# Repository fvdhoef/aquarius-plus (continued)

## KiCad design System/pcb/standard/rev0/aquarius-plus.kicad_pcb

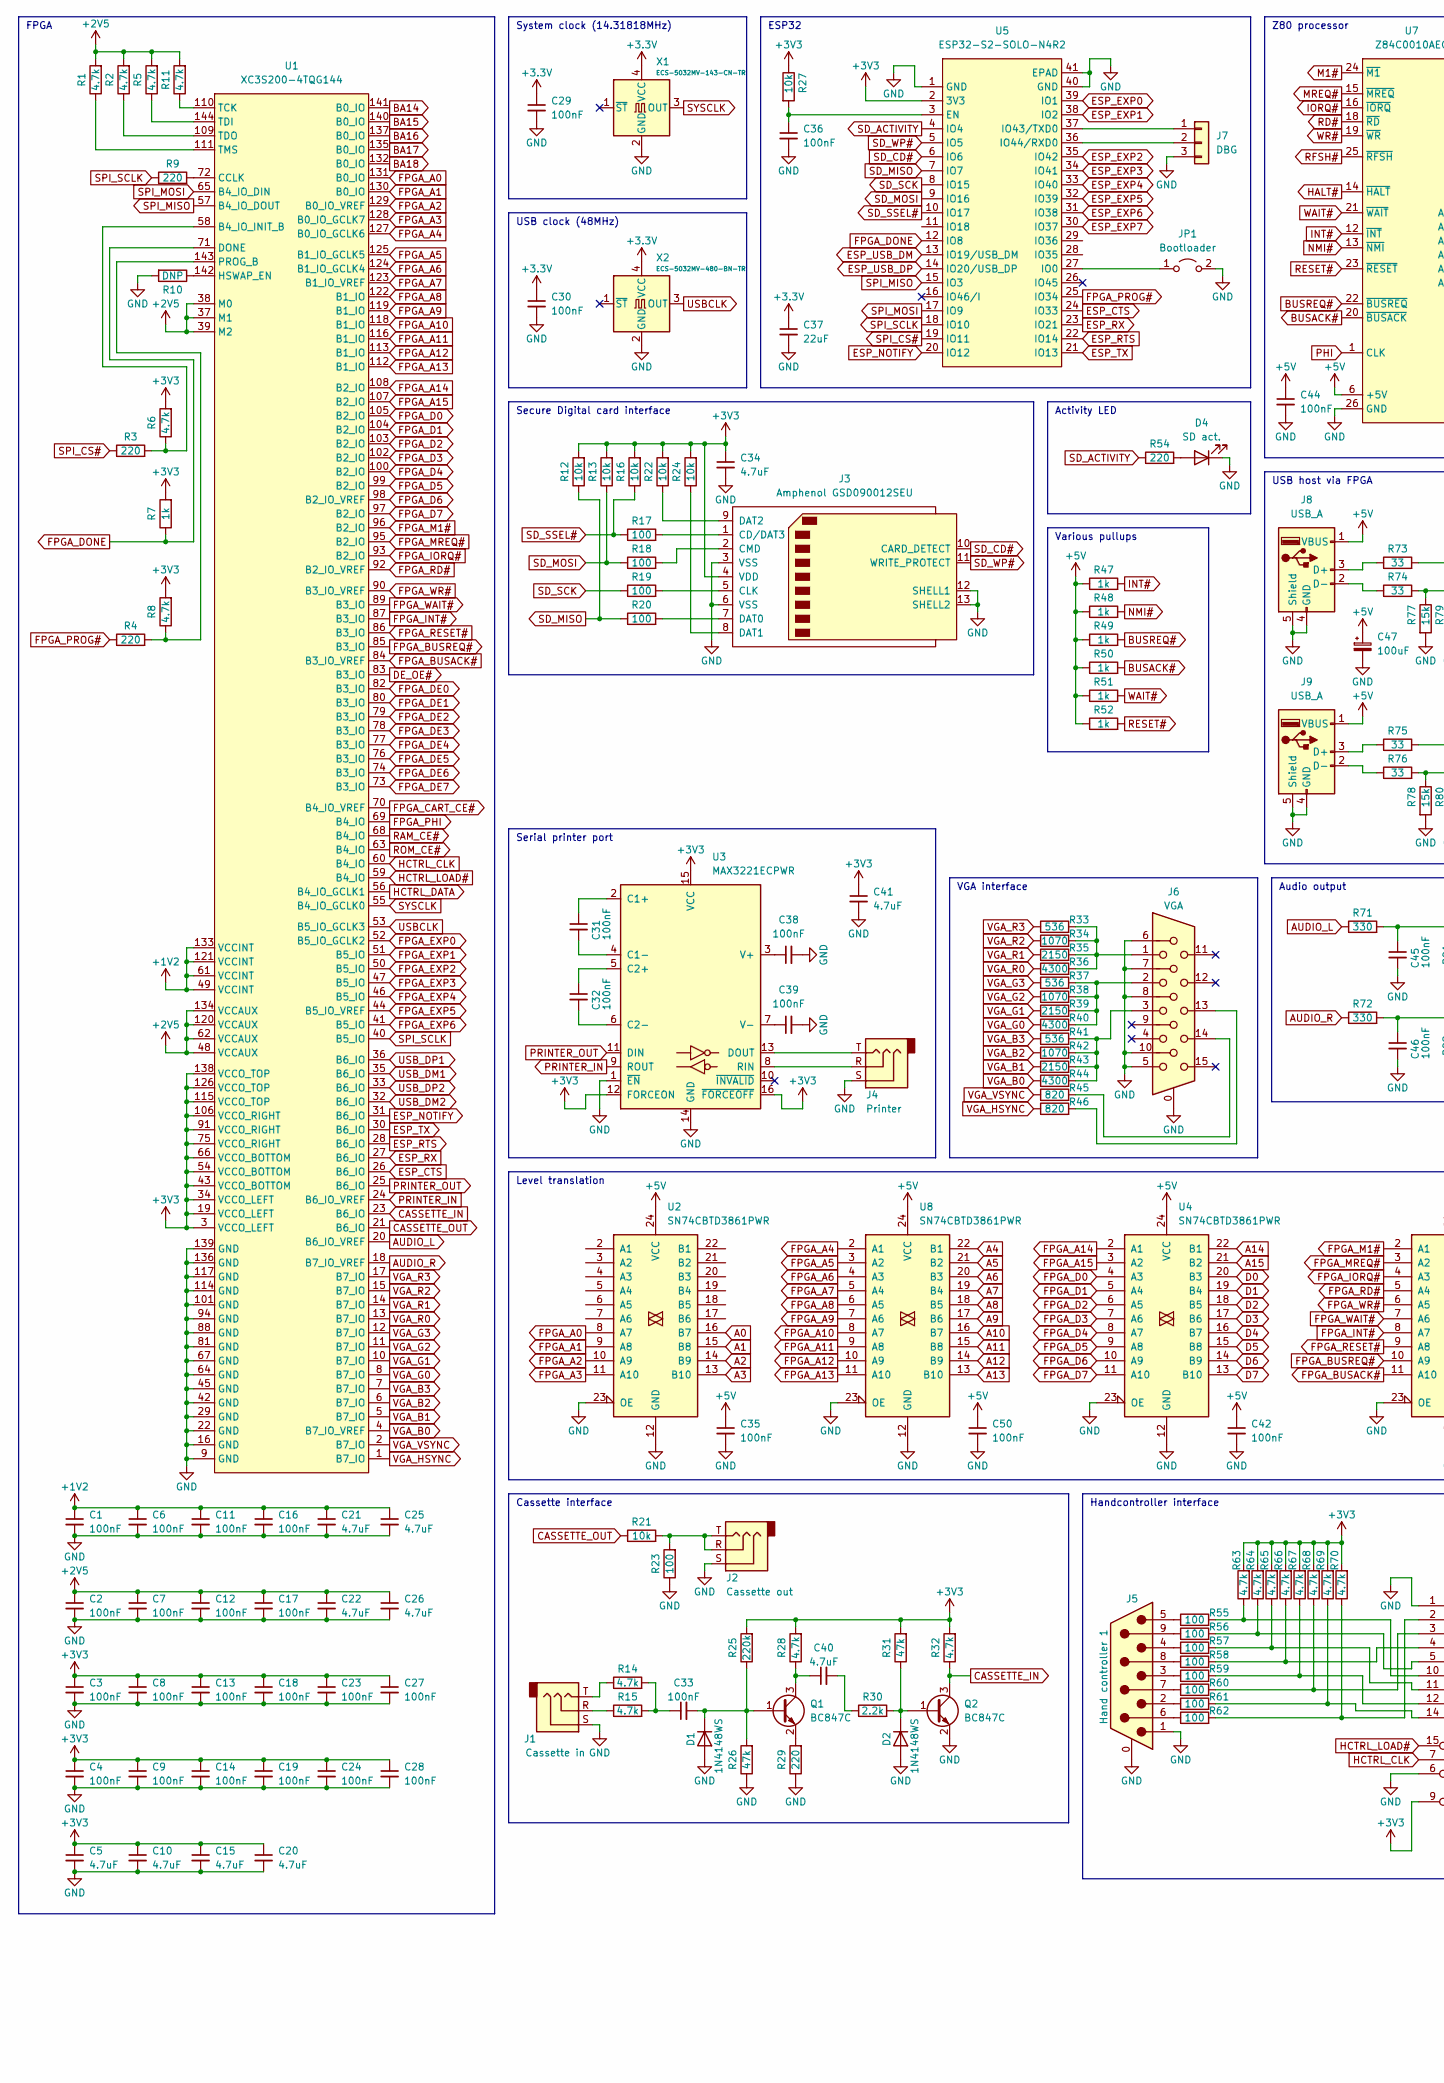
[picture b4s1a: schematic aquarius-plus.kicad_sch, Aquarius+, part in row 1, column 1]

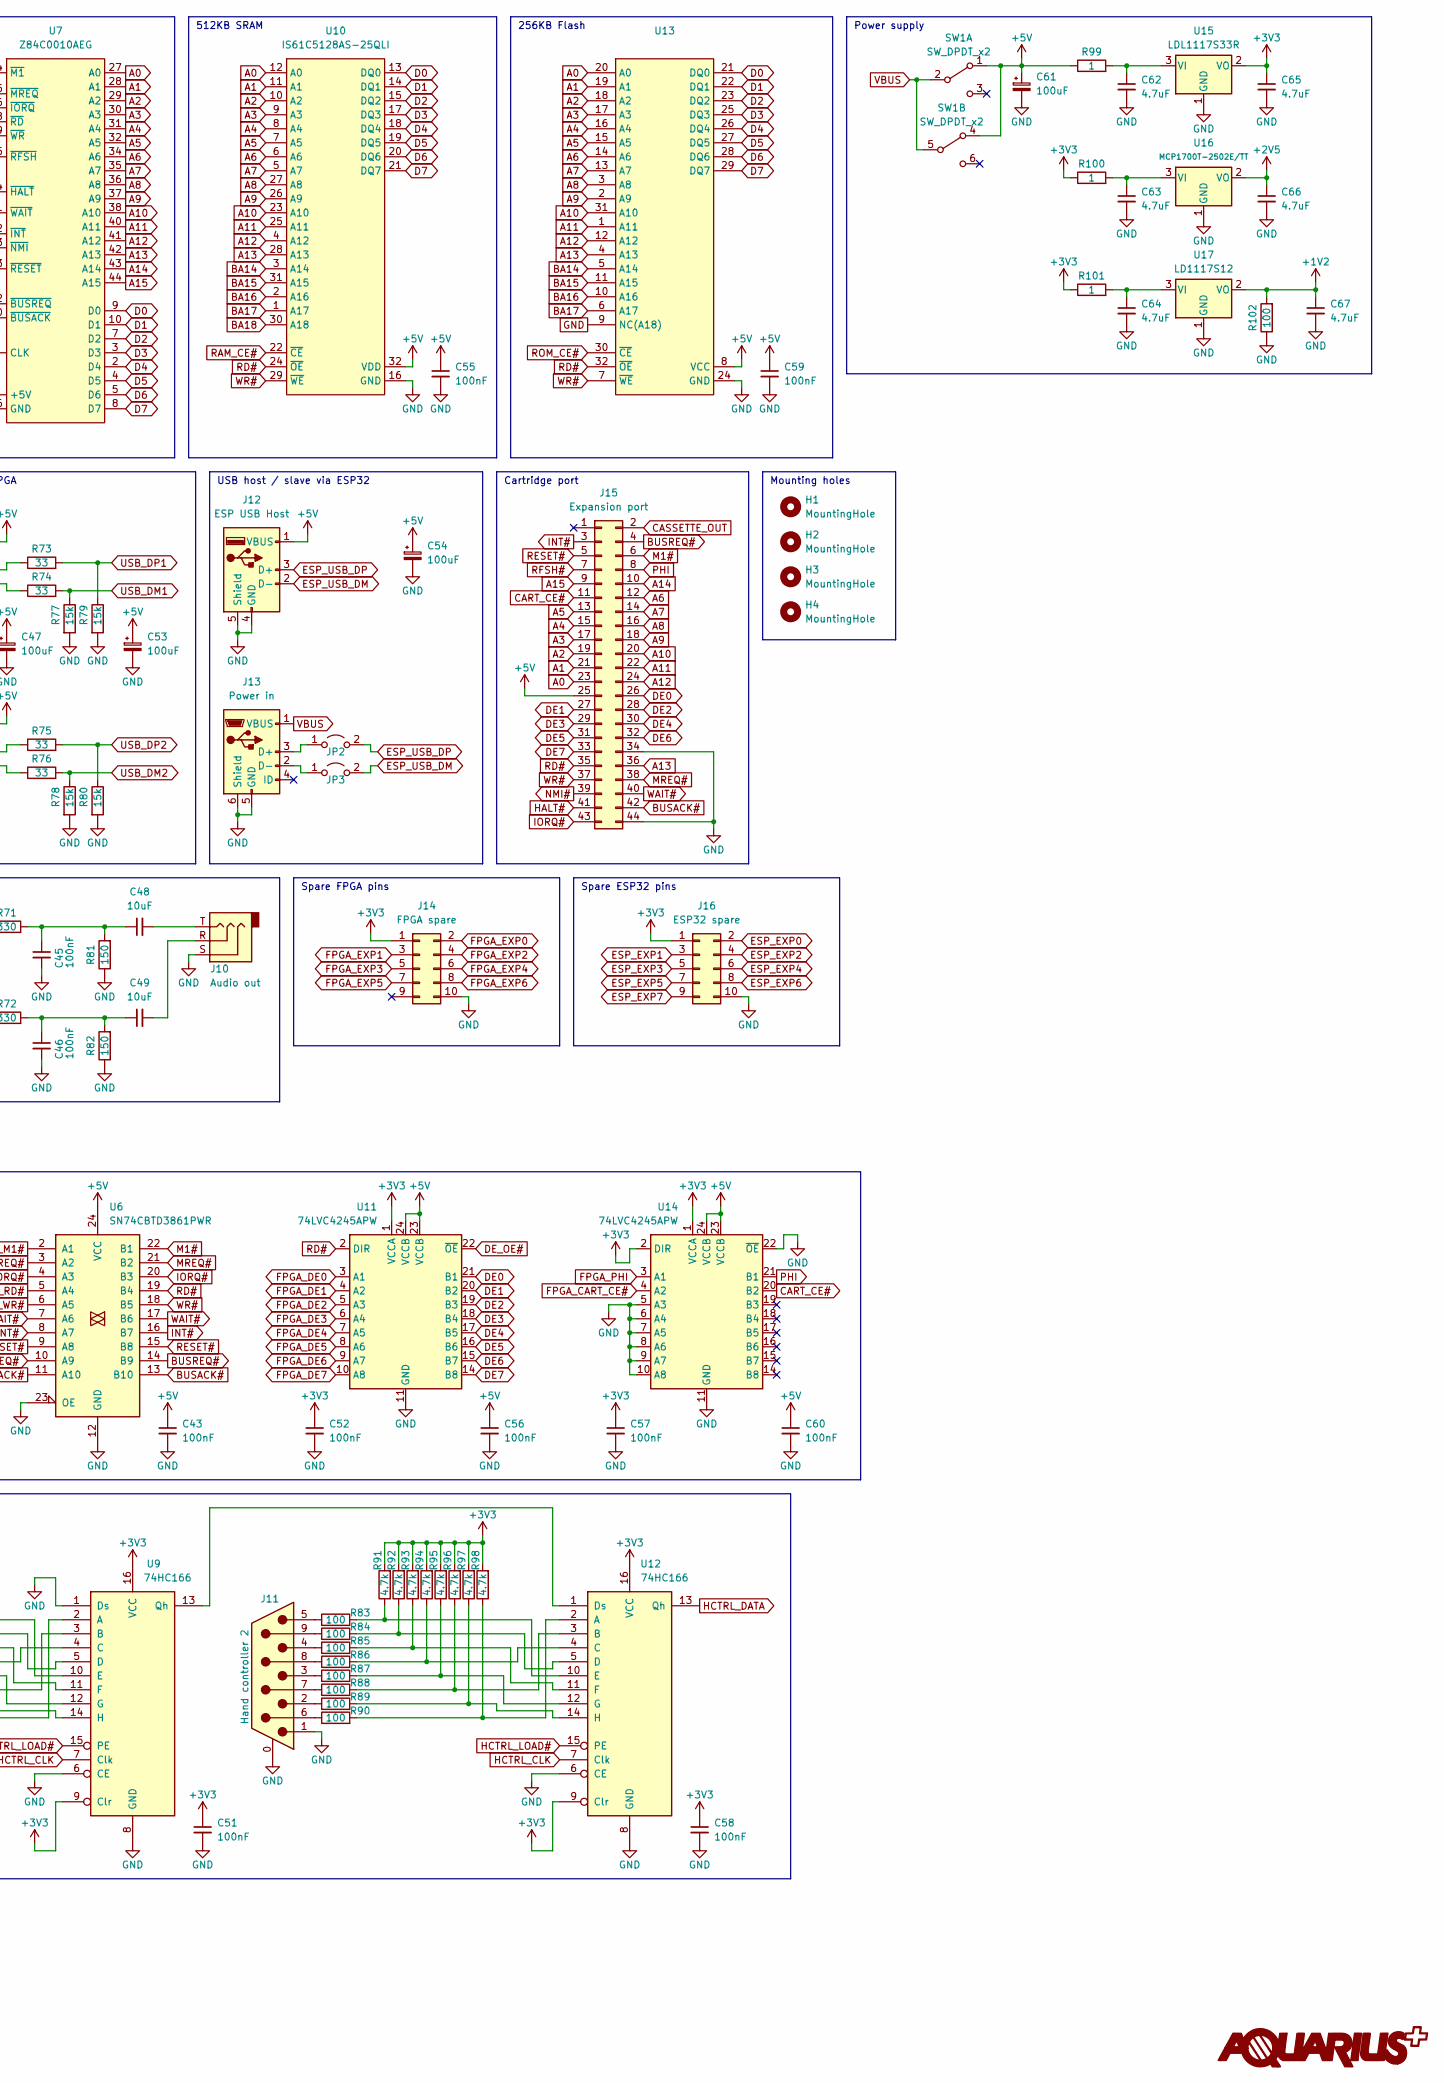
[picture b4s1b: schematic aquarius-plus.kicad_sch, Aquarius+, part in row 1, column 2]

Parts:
C1, C2, C3, C4, C6, C7, C8, C9, C11, C12, C13, C14, C16, C17, C18, C19, C23, C24, C27, C28, C29, C30, C31, C32, C33, C35, C36, C38, C39, C42, C43, C44, C45, C46, C50, C51, C52, C55, C56, C57, C58, C59, C60: 100nF; C_0603_1608Metric
C5, C10, C15, C20, C21, C22, C25, C26, C34, C40, C41, C62, C63, C64, C65, C66, C67: 4.7uF; C_0603_1608Metric
C37: 22uF; C_1206_3216Metric
C47, C53, C54, C61: 100uF; CP_Elec_6.3x7.7
C48, C49: 10uF; C_0805_2012Metric
D1, D2: 1N4148WS; D_SOD-323_HandSoldering
D4: SD act.; LED_D3.0mm_Horizontal_O1.27mm_Z2.0mm
H1, H2, H3, H4: MountingHole; MountingHole_3.2mm_M3
J1: Cassette in; Jack_3.5mm_CUI_SJ-3523-SMT_Horizontal
J2: Cassette out; Jack_3.5mm_CUI_SJ-3523-SMT_Horizontal
J3: Amphenol GSD090012SEU; SD_TE_2041021
J4: Printer; Jack_3.5mm_CUI_SJ-3523-SMT_Horizontal
J5: Hand controller 1; DSUB-9_Male_Horizontal_P2.77x2.84mm_EdgePinOffset9.90mm_Hou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
J6: VGA; ICD15S13E4GV00LF
J7: DBG; PinHeader_1x03_P2.54mm_Vertical
J8, J9: USB_A; USB_A_Molex_67643_Horizontal
J10: Audio out; Jack_3.5mm_CUI_SJ-3523-SMT_Horizontal
J11: Hand controller 2; DSUB-9_Male_Horizontal_P2.77x2.84mm_EdgePinOffset9.90mm_Hou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
J12: ESP USB Host; USB_A_Molex_67643_Horizontal
J13: Power in; 10118193-0001LF
J14: FPGA spare; PinHeader_2x05_P2.54mm_Vertical
J15: Expansion port; CR22A-44D-2.54DSA(70)
J16: ESP32 spare; PinHeader_2x05_P2.54mm_Vertical
JP1: Bootloader; PinHeader_1x02_P2.54mm_Vertical
JP2, JP3: USB; PinHeader_1x02_P2.54mm_Vertical
Q1, Q2: BC847C; SOT-23
R1, R2, R5, R6, R8, R11, R14, R15, R28, R32, R63, R64, R65, R66, R67, R68, R69, R70, R91, R92, R93, R94, R95, R96, R97, R98: 4.7k; R_0603_1608Metric
R3, R4, R9, R29, R54: 220; R_0603_1608Metric
R7, R47, R48, R49, R50, R51, R52: 1k; R_0603_1608Metric
R10: DNP; R_0603_1608Metric
R12, R13, R16, R21, R22, R24, R27: 10k; R_0603_1608Metric
R17, R18, R19, R20, R23, R55, R56, R57, R58, R59, R60, R61, R62, R83, R84, R85, R86, R87, R88, R89, R90, R102: 100; R_0603_1608Metric
R25: 220k; R_0603_1608Metric
R26, R31: 47k; R_0603_1608Metric
R30: 2.2k; R_0603_1608Metric
R33, R37, R41: 536; R_0603_1608Metric
R34, R38, R42: 1070; R_0603_1608Metric
R35, R39, R43: 2150; R_0603_1608Metric
R36, R40, R44: 4300; R_0603_1608Metric
R45, R46: 820; R_0603_1608Metric
R71, R72: 330; R_0603_1608Metric
R73, R74, R75, R76: 33; R_0603_1608Metric
R77, R78, R79, R80: 15k; R_0603_1608Metric
R81, R82: 150; R_0603_1608Metric
R99, R100, R101: 1; R_0603_1608Metric
SW1: SW_DPDT_x2; SW_E-Switch_EG2219_DPDT_Angled
U1: XC3S200-4TQG144; TQFP-144_20x20mm_P0.5mm
U2, U4, U6, U8: SN74CBTD3861PWR; TSSOP-24_4.4x7.8mm_P0.65mm
U3: MAX3221ECPWR; TSSOP-16_4.4x5mm_P0.65mm
U5: ESP32-S2-SOLO-N4R2
U7: Z84C0010AEG; LQFP-44_10x10mm_P0.8mm
U9, U12: 74HC166; SOIC-16_3.9x9.9mm_P1.27mm
U10: IS61C5128AS-25QLI; SSOP-32_11.305x20.495mm_P1.27mm
U11, U14: 74LVC4245APW; TSSOP-24_4.4x7.8mm_P0.65mm
U13: (no value)
U15: LDL1117S33R; SOT-223-3_TabPin2
U16: MCP1700T-2502E/TT; SOT-23
U17: LD1117S12; SOT-223-3_TabPin2
X1: ECS-5032MV-143-CN-TR; Oscillator_SMD_SeikoEpson_SG8002LB-4Pin_5.0x3.2mm
X2: ECS-5032MV-480-BN-TR; Oscillator_SMD_SeikoEpson_SG8002LB-4Pin_5.0x3.2mm

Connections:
+1V2: C1.1, C6.1, C11.1, C16.1, C21.1, C25.1, C67.1, R102.2, U1.49 (VCCINT), U1.61 (VCCINT), U1.121 (VCCINT), U1.133 (VCCINT), U17.2 (VO)
+2V5: C2.1, C7.1, C12.1, C17.1, C22.1, C26.1, C66.1, R1.2, R2.2, R5.2, R11.2, U1.37 (M1), U1.38 (M0), U1.39 (M2), U1.48 (VCCAUX), U1.62 (VCCAUX), U1.120 (VCCAUX), U1.134 (VCCAUX), U16.2 (VO)
+5V: C35.1, C42.1, C43.1, C44.1, C47.1, C50.1, C53.1, C54.1, C55.1, C56.1, C59.1, C60.1, C61.1, J8.1 (VBUS), J9.1 (VBUS), J12.1 (VBUS), J15.25, R47.1, R48.1, R49.1, R50.1, R51.1, R52.1, R99.1, SW1.1 (A), SW1.4 (A), U2.24 (VCC), U4.24 (VCC), U6.24 (VCC), U7.6 (+5V), U8.24 (VCC), U10.32 (VDD), U11.23 (VCCB), U11.24 (VCCB), U13.8 (VCC), U14.23 (VCCB), U14.24 (VCCB)
A0: J15.23, U2.16 (B7), U7.27 (A0), U10.12 (A0), U13.20 (A0)
A1: J15.21, U2.15 (B8), U7.28 (A1), U10.11 (A1), U13.19 (A1)
A2: J15.19, U2.14 (B9), U7.29 (A2), U10.10 (A2), U13.18 (A2)
A3: J15.17, U2.13 (B10), U7.30 (A3), U10.9 (A3), U13.17 (A3)
A4: J15.15, U7.31 (A4), U8.22 (B1), U10.8 (A4), U13.16 (A4)
A5: J15.13, U7.32 (A5), U8.21 (B2), U10.7 (A5), U13.15 (A5)
A6: J15.12, U7.34 (A6), U8.20 (B3), U10.6 (A6), U13.14 (A6)
A7: J15.14, U7.35 (A7), U8.19 (B4), U10.5 (A7), U13.13 (A7)
A8: J15.16, U7.36 (A8), U8.18 (B5), U10.27 (A8), U13.3 (A8)
A9: J15.18, U7.37 (A9), U8.17 (B6), U10.26 (A9), U13.2 (A9)
A10: J15.20, U7.38 (A10), U8.16 (B7), U10.23 (A10), U13.31 (A10)
A11: J15.22, U7.40 (A11), U8.15 (B8), U10.25 (A11), U13.1 (A11)
A12: J15.24, U7.41 (A12), U8.14 (B9), U10.4 (A12), U13.12 (A12)
A13: J15.36, U7.42 (A13), U8.13 (B10), U10.28 (A13), U13.4 (A13)
A14: J15.10, U4.22 (B1), U7.43 (A14)
A15: J15.9, U4.21 (B2), U7.44 (A15)
AUDIO_L: R71.1, U1.20 (B6_IO_VREF)
AUDIO_R: R72.1, U1.18 (B7_IO_VREF)
BA14: U1.141 (B0_IO), U10.3 (A14), U13.5 (A14)
BA15: U1.140 (B0_IO), U10.31 (A15), U13.11 (A15)
BA16: U1.137 (B0_IO), U10.2 (A16), U13.10 (A16)
BA17: U1.135 (B0_IO), U10.1 (A17), U13.6 (A17)
BA18: U1.132 (B0_IO), U10.30 (A18)
BUSACK#: J15.42, R50.2, U6.13 (B10), U7.20 (~BUSACK)
BUSREQ#: J15.4, R49.2, U6.14 (B9), U7.22 (~BUSREQ)
CART_CE#: J15.11, U14.20 (B2)
CASSETTE_IN: Q2.3 (C), R32.1, U1.23 (B6_IO)
CASSETTE_OUT: J15.2, R21.1, U1.21 (B6_IO)
D0: U4.20 (B3), U7.9 (D0), U10.13 (DQ0), U13.21 (DQ0)
D1: U4.19 (B4), U7.10 (D1), U10.14 (DQ1), U13.22 (DQ1)
D2: U4.18 (B5), U7.7 (D2), U10.15 (DQ2), U13.23 (DQ2)
D3: U4.17 (B6), U7.3 (D3), U10.17 (DQ3), U13.25 (DQ3)
D4: U4.16 (B7), U7.2 (D4), U10.18 (DQ4), U13.26 (DQ4)
D5: U4.15 (B8), U7.4 (D5), U10.19 (DQ5), U13.27 (DQ5)
D6: U4.14 (B9), U7.5 (D6), U10.20 (DQ6), U13.28 (DQ6)
D7: U4.13 (B10), U7.8 (D7), U10.21 (DQ7), U13.29 (DQ7)
DE0: J15.26, U11.21 (B1)
DE1: J15.27, U11.20 (B2)
DE2: J15.28, U11.19 (B3)
DE3: J15.29, U11.18 (B4)
DE4: J15.30, U11.17 (B5)
DE5: J15.31, U11.16 (B6)
DE6: J15.32, U11.15 (B7)
DE7: J15.33, U11.14 (B8)
DE_OE#: U1.83 (B3_IO), U11.22 (~OE)
ESP_CTS: U1.26 (B6_IO), U5.24 (IO33)
ESP_EXP0: J16.2, U5.39 (IO1)
ESP_EXP1: J16.3, U5.38 (IO2)
ESP_EXP2: J16.4, U5.35 (IO42)
ESP_EXP3: J16.5, U5.34 (IO41)
ESP_EXP4: J16.6, U5.33 (IO40)
ESP_EXP5: J16.7, U5.32 (IO39)
ESP_EXP6: J16.8, U5.31 (IO38)
ESP_EXP7: J16.9, U5.30 (IO37)
ESP_NOTIFY: U1.31 (B6_IO), U5.20 (IO12)
ESP_RTS: U1.28 (B6_IO), U5.22 (IO14)
ESP_RX: U1.27 (B6_IO), U5.23 (IO21)
ESP_TX: U1.30 (B6_IO), U5.21 (IO13)
ESP_USB_DM: J12.2 (D-), JP3.2 (B), U5.13 (IO19/USB_DM)
ESP_USB_DP: J12.3 (D+), JP2.2 (B), U5.14 (IO20/USB_DP)
FPGA_A0: U1.131 (B0_IO), U2.8 (A7)
FPGA_A1: U1.130 (B0_IO), U2.9 (A8)
FPGA_A2: U1.129 (B0_IO_VREF), U2.10 (A9)
FPGA_A3: U1.128 (B0_IO_GCLK7), U2.11 (A10)
FPGA_A4: U1.127 (B0_IO_GCLK6), U8.2 (A1)
FPGA_A5: U1.125 (B1_IO_GCLK5), U8.3 (A2)
FPGA_A6: U1.124 (B1_IO_GCLK4), U8.4 (A3)
FPGA_A7: U1.123 (B1_IO_VREF), U8.5 (A4)
FPGA_A8: U1.122 (B1_IO), U8.6 (A5)
FPGA_A9: U1.119 (B1_IO), U8.7 (A6)
FPGA_A10: U1.118 (B1_IO), U8.8 (A7)
FPGA_A11: U1.116 (B1_IO), U8.9 (A8)
FPGA_A12: U1.113 (B1_IO), U8.10 (A9)
FPGA_A13: U1.112 (B1_IO), U8.11 (A10)
FPGA_A14: U1.108 (B2_IO), U4.2 (A1)
FPGA_A15: U1.107 (B2_IO), U4.3 (A2)
FPGA_BUSACK#: U1.84 (B3_IO_VREF), U6.11 (A10)
FPGA_BUSREQ#: U1.85 (B3_IO), U6.10 (A9)
FPGA_CART_CE#: U1.70 (B4_IO_VREF), U14.4 (A2)
FPGA_D0: U1.105 (B2_IO), U4.4 (A3)
FPGA_D1: U1.104 (B2_IO), U4.5 (A4)
FPGA_D2: U1.103 (B2_IO), U4.6 (A5)
FPGA_D3: U1.102 (B2_IO), U4.7 (A6)
FPGA_D4: U1.100 (B2_IO), U4.8 (A7)
FPGA_D5: U1.99 (B2_IO), U4.9 (A8)
FPGA_D6: U1.98 (B2_IO_VREF), U4.10 (A9)
FPGA_D7: U1.97 (B2_IO), U4.11 (A10)
FPGA_DE0: U1.82 (B3_IO), U11.3 (A1)
FPGA_DE1: U1.80 (B3_IO), U11.4 (A2)
FPGA_DE2: U1.79 (B3_IO), U11.5 (A3)
FPGA_DE3: U1.78 (B3_IO), U11.6 (A4)
FPGA_DE4: U1.77 (B3_IO), U11.7 (A5)
FPGA_DE5: U1.76 (B3_IO), U11.8 (A6)
FPGA_DE6: U1.74 (B3_IO), U11.9 (A7)
FPGA_DE7: U1.73 (B3_IO), U11.10 (A8)
FPGA_DONE: R7.1, U1.71 (DONE), U5.12 (IO8)
FPGA_EXP0: J14.2, U1.52 (B5_IO_GCLK2)
FPGA_EXP1: J14.3, U1.51 (B5_IO)
FPGA_EXP2: J14.4, U1.50 (B5_IO)
FPGA_EXP3: J14.5, U1.47 (B5_IO)
FPGA_EXP4: J14.6, U1.46 (B5_IO)
FPGA_EXP5: J14.7, U1.44 (B5_IO_VREF)
FPGA_EXP6: J14.8, U1.41 (B5_IO)
FPGA_INT#: U1.87 (B3_IO), U6.8 (A7)
FPGA_IORQ#: U1.93 (B2_IO), U6.4 (A3)
FPGA_M1#: U1.96 (B2_IO), U6.2 (A1)
FPGA_MREQ#: U1.95 (B2_IO), U6.3 (A2)
FPGA_PHI: U1.69 (B4_IO), U14.3 (A1)
FPGA_PROG#: R4.1, U5.25 (IO34)
FPGA_RD#: U1.92 (B2_IO_VREF), U6.5 (A4)
FPGA_RESET#: U1.86 (B3_IO), U6.9 (A8)
FPGA_WAIT#: U1.89 (B3_IO), U6.7 (A6)
FPGA_WR#: U1.90 (B3_IO_VREF), U6.6 (A5)
GND: C1.2, C2.2, C3.2, C4.2, C5.2, C6.2, C7.2, C8.2, C9.2, C10.2, C11.2, C12.2, C13.2, C14.2, C15.2, C16.2, C17.2, C18.2, C19.2, C20.2, C21.2, C22.2, C23.2, C24.2, C25.2, C26.2, C27.2, C28.2, C29.2, C30.2, C34.2, C35.2, C36.2, C37.2, C38.2, C39.2, C41.2, C42.2, C43.2, C44.2, C45.2, C46.2, C47.2, C50.2, C51.2, C52.2, C53.2, C54.2, C55.2, C56.2, C57.2, C58.2, C59.2, C60.2, C61.2, C62.2, C63.2, C64.2, C65.2, C66.2, C67.2, D1.2 (A), D2.2 (A), D4.1 (K), J1.S, J2.S, J3.3 (VSS), J3.6 (VSS), J3.12 (SHELL1), J3.13 (SHELL2), J4.S, J5.0 (PAD), J5.1, J6.0, J6.5, J6.6, J6.7, J6.8, J6.10, J7.3, J8.4 (GND), J8.5 (Shield), J9.4 (GND), J9.5 (Shield), J10.S, J11.0 (PAD), J11.1, J12.4 (GND), J12.5 (Shield), J13.5 (GND), J13.6 (Shield), J14.10, J15.34, J15.44, J16.10, JP1.2 (B), Q2.2 (E), R10.2, R23.1, R26.1, R29.1, R77.2, R78.2, R79.2, R80.2, R81.1, R82.1, R102.1, U1.9 (GND), U1.16 (GND), U1.22 (GND), U1.29 (GND), U1.42 (GND), U1.45 (GND), U1.64 (GND), U1.67 (GND), U1.81 (GND), U1.88 (GND), U1.94 (GND), U1.101 (GND), U1.114 (GND), U1.117 (GND), U1.136 (GND), U1.139 (GND), U2.12 (GND), U2.23 (OE), U3.1 (~EN), U3.14 (GND), U4.12 (GND), U4.23 (OE), U5.1 (GND), U5.40 (GND), U5.41 (EPAD), U6.12 (GND), U6.23 (OE), U7.26 (GND), U8.12 (GND), U8.23 (OE), U9.1 (Ds), U9.6 (CE), U9.8 (GND), U10.16 (GND), U11.11 (GND), U11.12 (GND), U11.13 (GND), U12.6 (CE), U12.8 (GND), U13.9 (NC(A18)), U13.24 (GND), U14.5 (A3), U14.6 (A4), U14.7 (A5), U14.8 (A6), U14.9 (A7), U14.10 (A8), U14.11 (GND), U14.12 (GND), U14.13 (GND), U14.22 (~OE), U15.1 (GND), U16.1 (GND), U17.1 (GND), X1.2 (GND), X2.2 (GND)
HALT#: J15.41, U7.14 (~HALT)
HCTRL_CLK: U1.60 (B4_IO), U9.7 (Clk), U12.7 (Clk)
HCTRL_DATA: U1.56 (B4_IO_GCLK1), U12.13 (Qh)
HCTRL_LOAD#: U1.59 (B4_IO), U9.15 (PE), U12.15 (PE)
INT#: J15.3, R47.2, U6.16 (B7), U7.12 (~INT)
IORQ#: J15.43, U6.20 (B3), U7.16 (~IORQ)
M1#: J15.6, U6.22 (B1), U7.24 (~M1)
MREQ#: J15.38, U6.21 (B2), U7.15 (~MREQ)
NMI#: J15.39, R48.2, U7.13 (~NMI)
unnamed: C31.1, U3.2 (C1+)
unnamed: C31.2, U3.4 (C1-)
unnamed: C32.1, U3.5 (C2+)
unnamed: C32.2, U3.6 (C2-)
unnamed: C33.1, R14.2, R15.2
unnamed: C33.2, D1.1 (K), Q1.1 (B), R25.1, R26.2
unnamed: C36.1, R27.2, U5.3 (EN)
unnamed: C38.1, U3.3 (V+)
unnamed: C39.1, U3.7 (V-)
unnamed: C40.1, Q1.3 (C), R28.1
unnamed: C40.2, R30.1
unnamed: C45.1, C48.1, R71.2, R81.2
unnamed: C46.1, C49.1, R72.2, R82.2
unnamed: C48.2, J10.T
unnamed: C49.2, J10.R
unnamed: C62.1, R99.2, U15.3 (VI)
unnamed: C63.1, R100.2, U16.3 (VI)
unnamed: C64.1, R101.2, U17.3 (VI)
unnamed: D2.1 (K), Q2.1 (B), R30.2, R31.1
unnamed: D4.2 (A), R54.2
unnamed: J1.R, R15.1
unnamed: J1.T, R14.1
unnamed: J2.R, J2.T, R21.2, R23.2
unnamed: J3.1 (CD/DAT3), R17.2
unnamed: J3.2 (CMD), R18.2
unnamed: J3.5 (CLK), R19.2
unnamed: J3.7 (DAT0), R20.2
unnamed: J3.8 (DAT1), R24.1
unnamed: J3.9 (DAT2), R22.1
unnamed: J4.R, U3.8 (RIN)
unnamed: J4.T, U3.13 (DOUT)
unnamed: J5.2, R61.1
unnamed: J5.3, R59.1
unnamed: J5.4, R57.1
unnamed: J5.5, R55.1
unnamed: J5.6, R62.1
unnamed: J5.7, R60.1
unnamed: J5.8, R58.1
unnamed: J5.9, R56.1
unnamed: J6.1, R33.2, R34.2, R35.2, R36.2
unnamed: J6.2, R37.2, R38.2, R39.2, R40.2
unnamed: J6.3, R41.2, R42.2, R43.2, R44.2
unnamed: J6.13, R46.2
unnamed: J6.14, R45.2
unnamed: J7.1, U5.37 (IO32/TXD0)
unnamed: J7.2, U5.36 (IO44/RXD0)
unnamed: J8.2 (D-), R74.1
unnamed: J8.3 (D+), R73.1
unnamed: J9.2 (D-), R76.1
unnamed: J9.3 (D+), R75.1
unnamed: J11.2, R89.1
unnamed: J11.3, R87.1
unnamed: J11.4, R85.1
unnamed: J11.5, R83.1
unnamed: J11.6, R90.1
unnamed: J11.7, R88.1
unnamed: J11.8, R86.1
unnamed: J11.9, R84.1
unnamed: J13.2 (D-), JP3.1 (A)
unnamed: J13.3 (D+), JP2.1 (A)
unnamed: JP1.1 (A), U5.27 (IO0)
unnamed: Q1.2 (E), R29.2
unnamed: R1.1, U1.111 (TMS)
unnamed: R2.1, U1.109 (TDO)
unnamed: R3.2, R6.1, U1.58 (B4_IO_INIT_B)
unnamed: R4.2, R8.1, U1.143 (PROG_B)
unnamed: R5.1, U1.144 (TDI)
unnamed: R9.2, U1.72 (CCLK)
unnamed: R10.1, U1.142 (HSWAP_EN)
unnamed: R11.1, U1.110 (TCK)
unnamed: R55.2, R63.1, U9.10 (E)
unnamed: R56.2, R64.1, U9.5 (D)
unnamed: R57.2, R65.1, U9.11 (F)
unnamed: R58.2, R66.1, U9.4 (C)
unnamed: R59.2, R67.1, U9.12 (G)
unnamed: R60.2, R68.1, U9.3 (B)
unnamed: R61.2, R69.1, U9.14 (H)
unnamed: R62.2, R70.1, U9.2 (A)
unnamed: R83.2, R91.1, U12.10 (E)
unnamed: R84.2, R92.1, U12.5 (D)
unnamed: R85.2, R93.1, U12.11 (F)
unnamed: R86.2, R94.1, U12.4 (C)
unnamed: R87.2, R95.1, U12.12 (G)
unnamed: R88.2, R96.1, U12.3 (B)
unnamed: R89.2, R97.1, U12.14 (H)
unnamed: R90.2, R98.1, U12.2 (A)
unnamed: U9.13 (Qh), U12.1 (Ds)
PHI: J15.8, U7.1 (CLK), U14.21 (B1)
PRINTER_IN: U1.24 (B6_IO_VREF), U3.9 (ROUT)
PRINTER_OUT: U1.25 (B6_IO), U3.11 (DIN)
RAM_CE#: U1.68 (B4_IO), U10.22 (~CE)
RD#: J15.35, U6.19 (B4), U7.18 (~RD), U10.24 (~OE), U11.2 (DIR), U13.32 (~OE)
RESET#: J15.5, R52.2, U6.15 (B8), U7.23 (~RESET)
RFSH#: J15.7, U7.25 (~RFSH)
ROM_CE#: U1.63 (B4_IO), U13.30 (~CE)
SD_ACTIVITY: R54.1, U5.4 (IO4)
SD_CD#: J3.10 (CARD_DETECT), U5.6 (IO6)
SD_MISO: R12.1, R20.1, U5.7 (IO7)
SD_MOSI: R13.1, R18.1, U5.9 (IO16)
SD_SCK: R19.1, U5.8 (IO15)
SD_SSEL#: R16.1, R17.1, U5.10 (IO17)
SD_WP#: J3.11 (WRITE_PROTECT), U5.5 (IO5)
SPI_CS#: R3.1, U5.19 (IO11)
SPI_MISO: U1.57 (B4_IO_DOUT), U5.15 (IO3)
SPI_MOSI: U1.65 (B4_IO_DIN), U5.17 (IO9)
SYSCLK: U1.55 (B4_IO_GCLK0), X1.3 (OUT)
USBCLK: U1.53 (B5_IO_GCLK3), X2.3 (OUT)
USB_DM1: R74.2, R77.1, U1.35 (B6_IO)
USB_DM2: R76.2, R78.1, U1.32 (B6_IO)
USB_DP1: R73.2, R79.1, U1.36 (B6_IO)
USB_DP2: R75.2, R80.1, U1.33 (B6_IO)
VBUS: J13.1 (VBUS), SW1.2 (B), SW1.5 (B)
VGA_B0: R44.1, U1.4 (B7_IO_VREF)
VGA_B1: R43.1, U1.5 (B7_IO)
VGA_B2: R42.1, U1.6 (B7_IO)
VGA_B3: R41.1, U1.7 (B7_IO)
VGA_G0: R40.1, U1.8 (B7_IO)
VGA_G1: R39.1, U1.10 (B7_IO)
VGA_G2: R38.1, U1.11 (B7_IO)
VGA_G3: R37.1, U1.12 (B7_IO)
VGA_HSYNC: R46.1, U1.1 (B7_IO)
VGA_R0: R36.1, U1.13 (B7_IO)
VGA_R1: R35.1, U1.14 (B7_IO)
VGA_R2: R34.1, U1.15 (B7_IO)
VGA_R3: R33.1, U1.17 (B7_IO)
VGA_VSYNC: R45.1, U1.2 (B7_IO)
WAIT#: J15.40, R51.2, U6.17 (B6), U7.21 (~WAIT)
WR#: J15.37, U6.18 (B5), U7.19 (~WR), U10.29 (~WE), U13.7 (~WE)

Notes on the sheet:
Level translation
System clock (14.31818MHz)
USB host / slave via ESP32
USB clock (48MHz)
Various pullups
Audio output
Activity LED
Cartridge port
Serial printer port
Power supply
Spare FPGA pins
Cassette interface
ESP32
256KB Flash
512KB SRAM
Z80 processor
FPGA
Spare ESP32 pins
VGA interface
Mounting holes
Secure Digital card interface
USB host via FPGA
Handcontroller interface

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
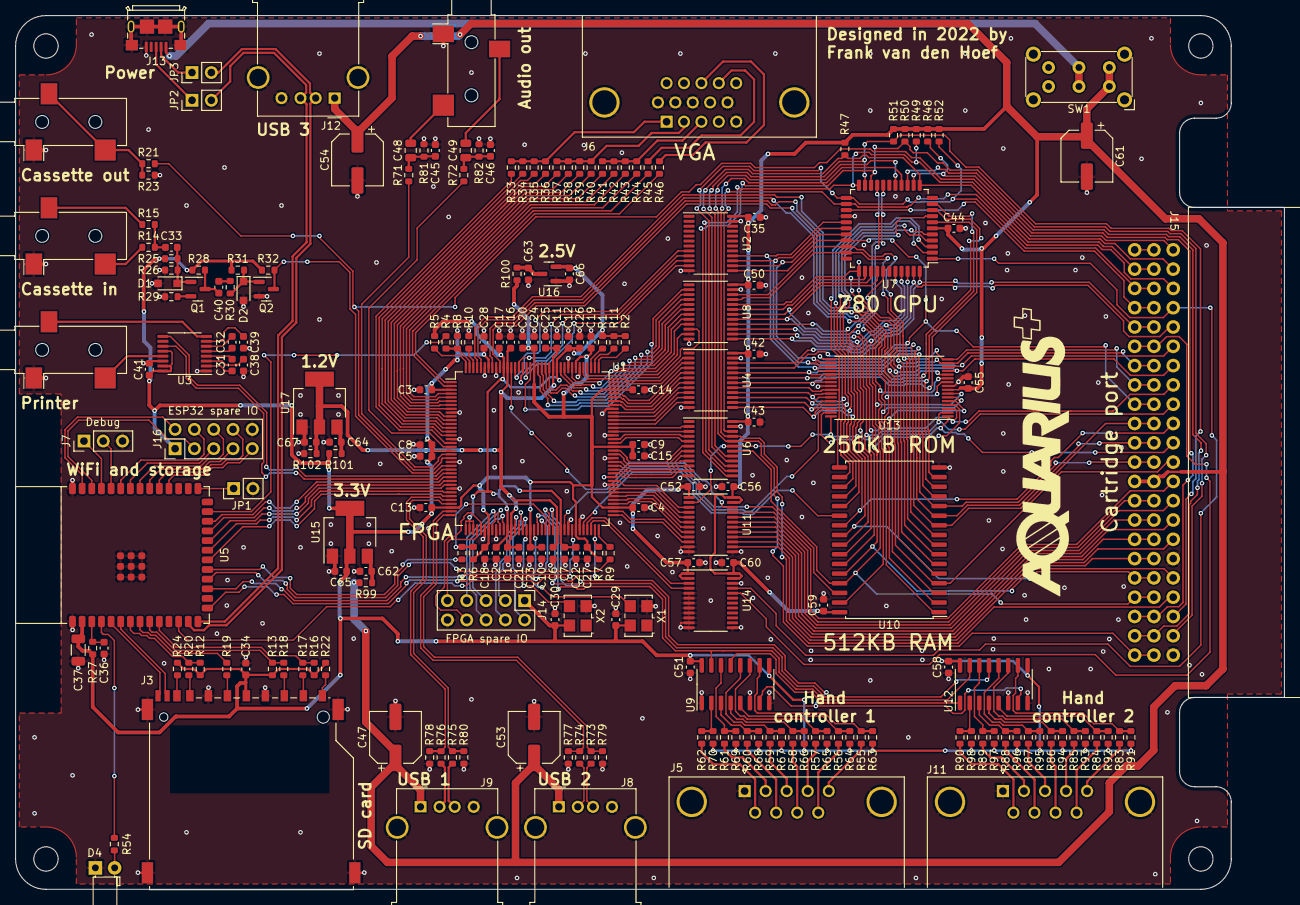
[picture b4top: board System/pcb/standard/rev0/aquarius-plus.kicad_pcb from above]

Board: 2 copper layers, 167.0 x 115.0 mm, 216 parts (0 on the bottom side), 257 nets.
